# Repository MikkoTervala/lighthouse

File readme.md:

# Lighthouse

### Lighthouse for Family Connection

#### See also: [lighthouse-firmware](https://github.com/MikkoTervala/lighthouse-firmware)

**Lighthouse** is a connected smart decoration that synchronizes over the internet to let your family know when you're home.

## Views and Schematics

- **[🌐 Schematic View](https://kicanvas.org/?github=https%3A%2F%2Fgithub.com%2FMikkoTervala%2Flighthouse%2Fblob%2Fmain%2Fpcb%2Flighthouse-pcb.kicad_sch)**

- **[🌐 Board Layout](https://kicanvas.org/?github=https%3A%2F%2Fgithub.com%2FMikkoTervala%2Flighthouse%2Fblob%2Fmain%2Fpcb%2Flighthouse-pcb.kicad_pcb)**

- **[🌐 Interactive 3D View](https://3dviewer.net/index.html#model=https://raw.githubusercontent.com/MikkoTervala/lighthouse/refs/heads/main/pcb/lighthouse-pcb.step)**

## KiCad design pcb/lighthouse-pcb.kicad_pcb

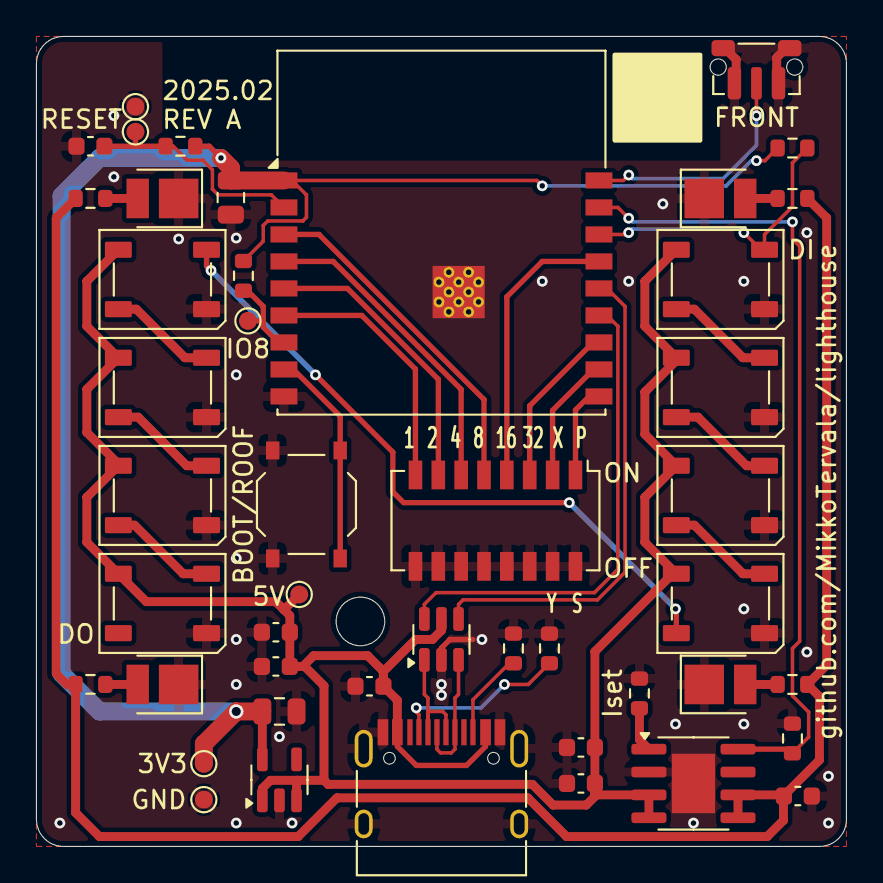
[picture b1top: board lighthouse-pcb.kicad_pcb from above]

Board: 2 copper layers, 45.0 x 45.0 mm, 51 parts (0 on the bottom side), 36 nets.

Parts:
C1: 1µF; C_0603_1608Metric
C3, C6: 10µf; C_0805_2012Metric
C4, C5, C8, C9: 2.2µf; C_0603_1608Metric
C7, C10: 220nf; C_0603_1608Metric
D2, D3, D4, D5, D6, D11, D12, D13: WS2812B; LED_WS2812B_PLCC4_5.0x5.0mm_P3.2mm
D7, D8, D9, D10: LED 0.5W 3000k; LED_PLCC_2835
H4: MountingHole M2.5; MountingHole_2.7mm_M2.5
J1: USB_C_Receptacle_USB2.0; USB_C_Receptacle_HRO_TYPE-C-31-M-12
R1, R2, R3, R13: 10k; R_0603_1608Metric
R5, R6: 5.1k; R_0603_1608Metric
R7, R8, R9, R10: 2; R_0603_1608Metric
R11: 3k; R_0603_1608Metric
SW1: BOOT/ROOF; SW_Push_1P1T_XKB_TS-1187A
SW3: FRONT; SW_Push_1P1T-MP_NO_Horizontal_Alps_SKRTLAE010
SW4: SW_DIP_x08; SW_DIP_SPSTx08_Slide_Copal_CHS-08A_W5.08mm_P1.27mm_JPin
T1, T2, T3, T4: Tab
TP1, TP5: GND; TestPoint_Pad_D1.0mm
TP2: 3V3; TestPoint_Pad_D1.0mm
TP3: RESET; TestPoint_Pad_D1.0mm_no_court
TP4: IO8; TestPoint_Pad_D1.0mm
TP6: 5V; TestPoint_Pad_D1.0mm
U1: ESP32-C3-WROOM-02
U2: CN5711; SOIC-8-1EP_3.9x4.9mm_P1.27mm_EP2.41x3.3mm
U3: AP2112K-3.3; SOT-23-5
U4: USBLC6-2SC6; SOT-23-6

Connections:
+3V3: C3.1, C6.1, R1.1, R2.1, R3.2, TP2.1, U1.1 (3V3), U3.5 (VOUT)
+5V: C4.1, C5.1, C8.1, C9.1, C10.1, D2.1 (VDD), D3.1 (VDD), D4.1 (VDD), D5.1 (VDD), D6.1 (VDD), D11.1 (VDD), D12.1 (VDD), D13.1 (VDD), J1.A4 (VBUS), J1.A9 (VBUS), J1.B4 (VBUS), J1.B9 (VBUS), TP6.1, U2.3 (VCC), U2.4 (VCC), U3.1 (VIN), U3.3 (EN), U4.5 (VBUS)
/BOOT: SW1.2, U1.8 (IO9)
/D+: J1.A6 (D+), J1.B6 (D+), U4.3 (I/O2)
/D-: J1.A7 (D-), J1.B7 (D-), U4.1 (I/O1)
/EN: C1.2, R2.2, TP3.1, U1.2 (EN)
GND: C1.1, C3.2, C4.2, C5.2, C6.2, C7.2, C8.2, C9.2, C10.2, D2.3 (VSS), D3.3 (VSS), D4.3 (VSS), D5.3 (VSS), D6.3 (VSS), D7.1 (K), D8.1 (K), D9.1 (K), D10.1 (K), D11.3 (VSS), D12.3 (VSS), D13.3 (VSS), J1.A1 (GND), J1.A12 (GND), J1.B1 (GND), J1.B12 (GND), J1.S1 (SHIELD), R5.2, R6.1, R11.2, R13.2, SW1.1, SW3.1, SW3.MP (Shield), SW4.9, SW4.10, SW4.11, SW4.12, SW4.13, SW4.14, SW4.15, SW4.16, TP1.1, TP5.1, U1.9 (GND), U1.19 (GND), U2.2 (GND), U2.9 (PAD), U3.2 (GND), U4.2 (GND)
GPIO0: SW3.2, U1.18 (IO0)
GPIO1: R13.1, U1.17 (IO1), U2.8 (CE)
GPIO2: D3.4 (DIN), R3.1, U1.16 (IO2)
GPIO3: SW4.4, U1.15 (IO3)
GPIO4: SW4.5, U1.3 (IO4)
GPIO5: SW4.6, U1.4 (IO5)
GPIO6: SW4.7, U1.5 (IO6)
GPIO7: SW4.8, U1.6 (IO7)
GPIO8: R1.2, TP4.1, U1.7 (IO8)
GPIO10: SW4.1, U1.10 (IO10)
unnamed: C7.1, R7.2, R8.2, R9.2, R10.2, U2.5 (LED), U2.6 (LED)
unnamed: D2.4 (DIN), D6.2 (DOUT)
unnamed: D3.2 (DOUT), D4.4 (DIN)
unnamed: D4.2 (DOUT), D5.4 (DIN)
unnamed: D5.2 (DOUT), D6.4 (DIN)
unnamed: D7.2 (A), R7.1
unnamed: D8.2 (A), R8.1
unnamed: D9.2 (A), R9.1
unnamed: D10.2 (A), R10.1
unnamed: D2.2 (DOUT), D11.4 (DIN)
unnamed: D11.2 (DOUT), D12.4 (DIN)
unnamed: D12.2 (DOUT), D13.4 (DIN)
unnamed: J1.A5 (CC1), R5.1
unnamed: J1.B5 (CC2), R6.2
unnamed: R11.1, U2.1 (ISET)
RX/20: SW4.2, U1.11 (IO20/RXD)
TX/21: SW4.3, U1.12 (IO21/TXD)
USB_D+: U1.14 (IO19), U4.4 (I/O2)
USB_D-: U1.13 (IO18), U4.6 (I/O1)

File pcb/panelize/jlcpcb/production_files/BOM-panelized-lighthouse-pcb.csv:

Comment,Designator,Footprint,LCSC,Quantity
1µF,C1,C_0603_1608Metric,C15849,1
10µf,"C3,C6",C_0805_2012Metric,C15850,2
USB_C_Receptacle_USB2.0,J1,USB_C_Receptacle_HRO_TYPE-C-31-M-12,C165948,1
220nf,"C10,C7",C_0603_1608Metric,C21120,2
2,"R10,R7,R8,R9",R_0603_1608Metric,C22977,4
5.1k,"R5,R6",R_0603_1608Metric,C23186,2
2.2µf,"C4,C5,C8,C9",C_0603_1608Metric,C23630,4
10k,"R1,R13,R2,R3",R_0603_1608Metric,C25804,4
WS2812B,"D11,D12,D13,D2,D3,D4,D5,D6",LED_WS2812B_PLCC4_5.0x5.0mm_P3.2mm,C2874885,8
ESP32-C3-WROOM-02,U1,ESP32-C3-WROOM-02,C2934560,1
BOOT/ROOF,SW1,SW_Push_1P1T_XKB_TS-1187A,C318885,1
SW_DIP_x08,SW4,SW_DIP_SPSTx08_Slide_Copal_CHS-08A_W5.08mm_P1.27mm_JPin,C3293147,1
CN5711,U2,SOIC-8-1EP_3.9x4.9mm_P1.27mm_EP2.41x3.3mm,C35634,1
3k,R11,R_0603_1608Metric,C4211,1
AP2112K-3.3,U3,SOT-23-5,C51118,1
FRONT,SW3,SW_Push_1P1T-MP_NO_Horizontal_Alps_SKRTLAE010,C561509,1
LED 0.5W 3000k,"D10,D7,D8,D9",LED_PLCC_2835,C694723,4
USBLC6-2SC6,U4,SOT-23-6,C7519,1

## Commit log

2025-01-29 Add symbols and footprints
2025-01-29 Initial schematic
2025-02-08 Layout and two button design
2025-02-09 Add footprints
2025-02-09 REV A release
2025-02-11 Update GPIO0-2 schematic and layout
2025-02-11 Added missing JLC part numbers and fixed U3 missing trace
2025-02-11 Add datamatrix location
2025-02-16 Remove identifier and tooling holes
2025-02-16 Remove tooling hole
2025-02-17 Add information for panelization
2025-02-17 Add panelized production file
2025-03-11 Cleanup measurements
2025-03-11 Add 3d export
2025-03-11 Add readme
2025-03-11 Add link to firmware repo
